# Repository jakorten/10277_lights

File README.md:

# LEGO set 10277 lights MOD
Custom Lightning for LEGO 10277 Ce 6/8" Crocodile

I have included the:
- Circuit Board
- Arduino source code both for:
* the ATTiny1616 (requires to install TinyCore and use of DPI interface (e.g. using Atmel ICE)
* a special i2c scanner for the UNO (detection of the module)
* an example control program (see video)

https://youtu.be/Wyeh1BkD_IM

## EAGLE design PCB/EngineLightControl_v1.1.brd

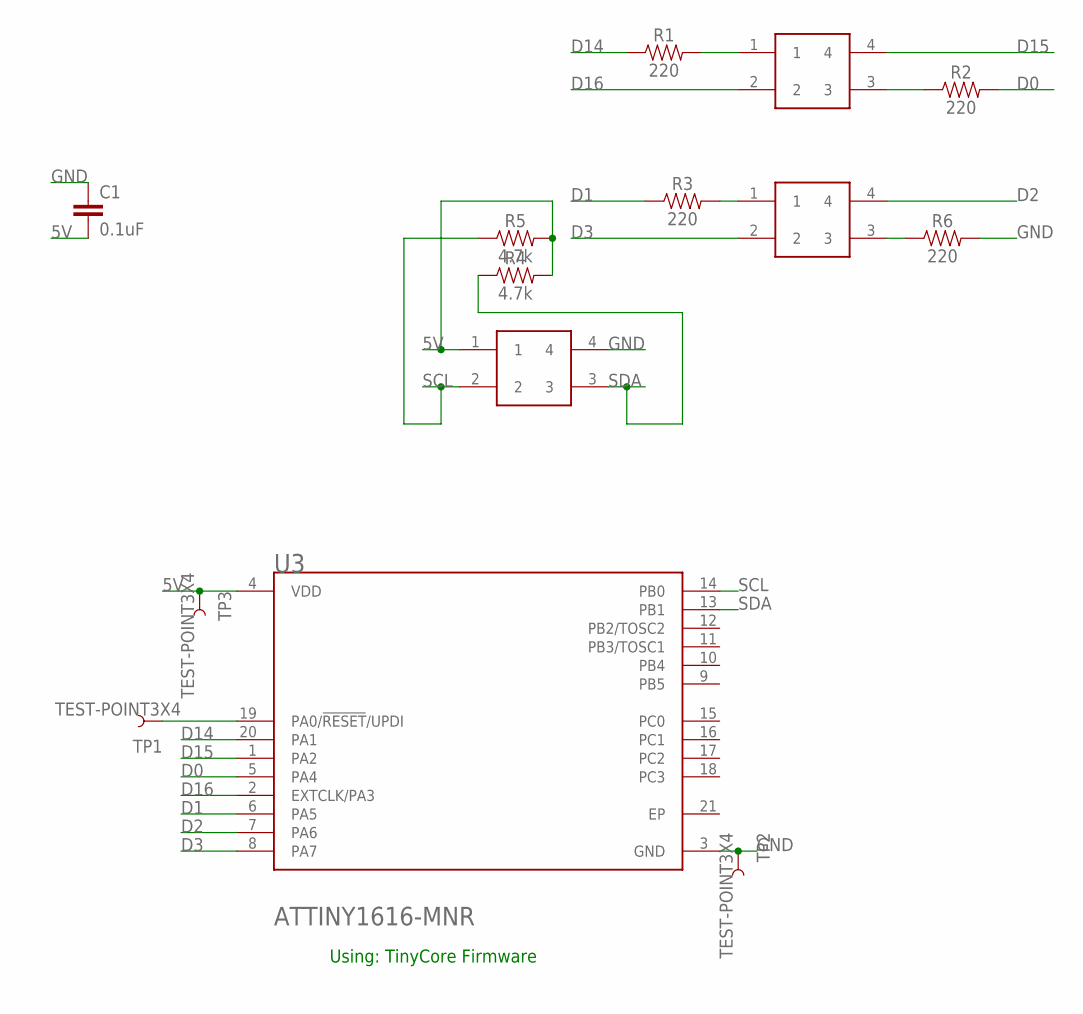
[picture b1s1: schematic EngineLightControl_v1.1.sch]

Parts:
C1: 0.1uF; 0603
R1, R2, R3, R6: 220; 0603
R4, R5: 4.7k; 0603
TP1, TP2, TP3: TEST-POINT3X4; PAD.03X.04
U3: MICROCHIP_ATTINY1616-MNRMICROCHIP_ATTINY1616-MNR_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; MICROCHIP_ATTINY1616-MNR_0
U$1, U$2, U$3: CONN_M04; CONN_04

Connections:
5V: C1.2, R4.2, R5.2, TP3.P$1, U3.4 (VDD), U$1.1
D0: R2.2, U3.5 (PA4)
D0_OUT: R2.1, U$2.3
D1: R3.1, U3.6 (PA5)
D1_OUT: R3.2, U$3.1
D2: U3.7 (PA6), U$3.4
D2_KATH: R6.1, U$3.3
D3: U3.8 (PA7), U$3.2
D14: R1.1, U3.20 (PA1)
D14_OUT: R1.2, U$2.1
D15: U3.1 (PA2), U$2.4
D16: U3.2 (EXTCLK/PA3), U$2.2
EP: U3.21 (EP)
GND: C1.1, R6.2, TP2.P$1, U3.3 (GND), U$1.4
SCL: R5.1, U3.14 (PB0), U$1.2
SDA: R4.1, U3.13 (PB1), U$1.3
UPDI: TP1.P$1, U3.19 (PA0/!RESET!/UPDI)

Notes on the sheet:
Using: TinyCore Firmware

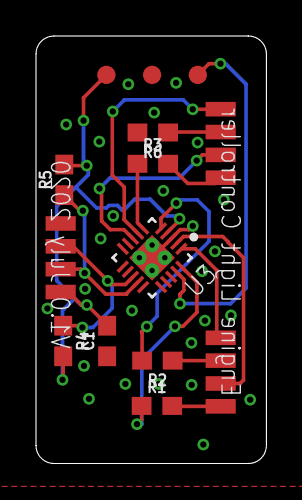
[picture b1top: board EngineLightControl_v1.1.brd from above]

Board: 2 copper layers, 12.8 x 23.8 mm, 14 parts (0 on the bottom side), 16 nets.

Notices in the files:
parts and their libraries:
SparkFun-Connectors: Licensing: Creative Commons ShareAlike 4.0 International - https://creativecommons.org/licenses/by-sa/4.0
